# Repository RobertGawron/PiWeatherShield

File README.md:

# Pi Weather Shield

## Purpose

Low-cost, easy-to-build hat Raspberry Pi that turns it into an indoor weather station. On the hardware side, it's a simple PCB with sensors I2C parts (BME280 and Si7021) and a small OLED screen to show the meassurements: temperature, humidity, and air pressure. On the software side there is a Rust app that handles the data and can send them via MQTT for furthr processing (using tools like Graphana and Home asistant).

The project can be integrated with the [Home Environment Monitor](https://github.com/RobertGawron/HomeEnvironmentMonitor), adding real-time graphs of the meassurements accessible from phone or PC.

## Hardware

This project is straightforward and includes the following I2C components:

* **Si7021:**
    * Temperature
    * Relative humidity
* **SGP30:**
    * TVOC (Total Volatile Organic Compounds)
    * eCO2 (equivalent CO2)
    * Raw hydrogen (H2) signal
    * Raw ethanol signal
* **BME280:**
    * Temperature
    * Relative humidity
    * Atmospheric pressure
* **SSD1306:** 0.91-inch 128x32 OLED display.

Tools: KiCad.

[More info.](./Hardware/README.md)

## Installation

The application is quite simple (just a couple of Python scripts) and could easily be developed directly on the Raspberry Pi, which is probably what most people would do for a small project like this. However, I’ve chosen a different approach -one that might seem like overkill- but it allows me to learn and apply DevOps.

We'll set up a local Docker environment capable of cross-compiling Docker images that contain our application, which will then be deployed to the Raspberry Pi.

Using Ansible, we will preconfigure the Raspberry Pi (install Docker, enable I2C, etc.) and deploy the Docker images to the Pi automatically.

[More info.](./DevOps/README.md)

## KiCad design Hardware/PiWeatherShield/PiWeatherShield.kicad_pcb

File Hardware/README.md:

## Hardware Overview

#### I2C Addresses:

* Si7021: 0x40
* SGP30: 0x58
* BME280:
    * 0x76 (when the SDO pin is grounded)
    * 0x77 (when the SDO pin is connected to VCC)
* SSD1306: 0x3C or 0x3D, depending on the PCB design.

## Tools

The PCB diagram was designed using KiCad.

## Links

* [Raspberry Pi pinout](https://www.raspberrypi.com/documentation/computers/images/GPIO-Pinout-Diagram-2.png?hash=df7d7847c57a1ca6d5b2617695de6d46)

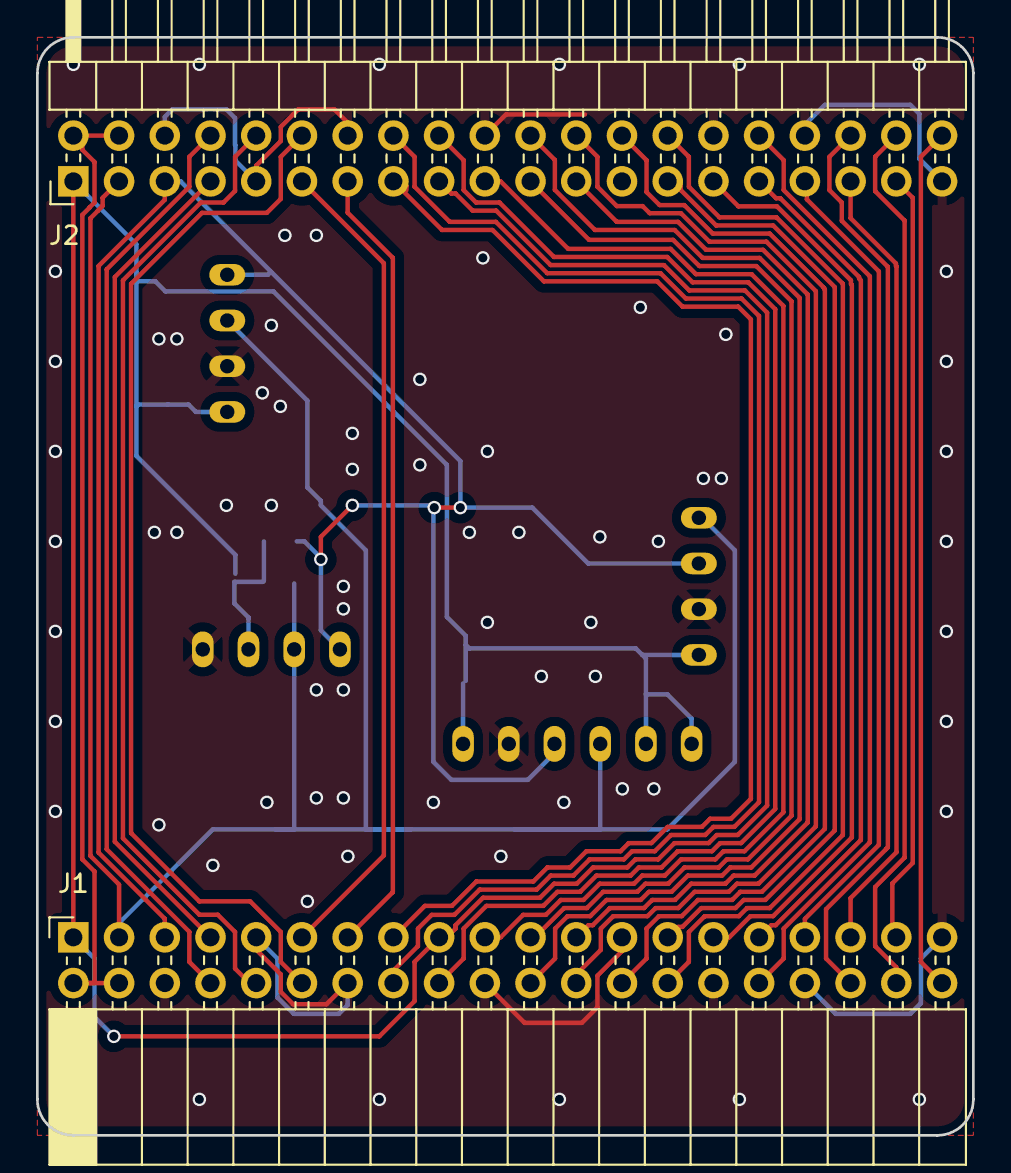
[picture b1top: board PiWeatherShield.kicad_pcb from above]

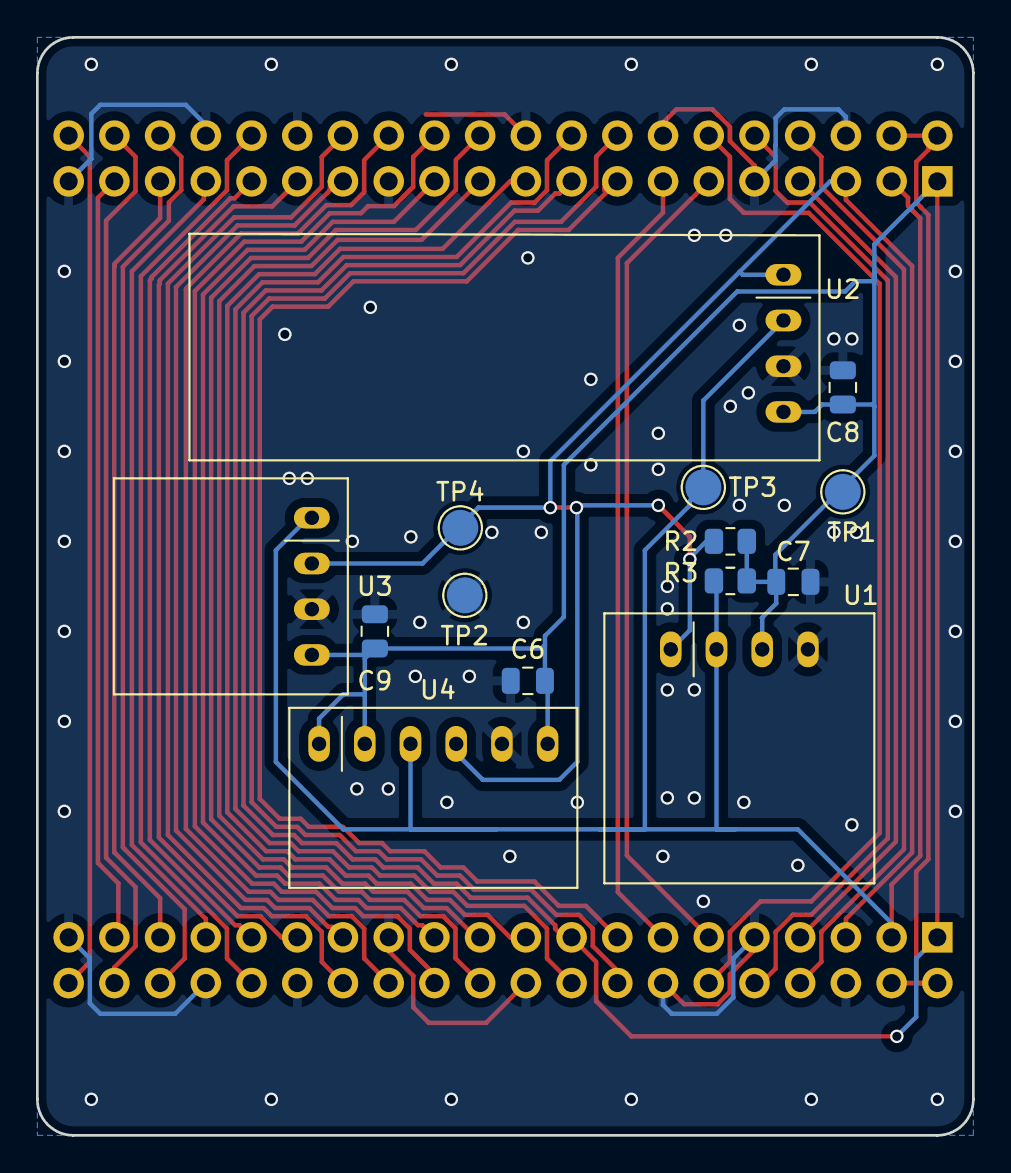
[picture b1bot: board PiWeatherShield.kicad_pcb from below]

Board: 2 copper layers, 52.0 x 61.0 mm, 16 parts (14 on the bottom side), 31 nets.

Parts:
C6, C7, C8, C9: 100n; C_0805_2012Metric
J1: Conn_02x20_Odd_Even; PinSocket_2x20_P2.54mm_Horizontal
J2: Conn_02x20_Odd_Even; PinHeader_2x20_P2.54mm_Horizontal
R2, R3: 2k2; R_0805_2012Metric
TP1, TP2, TP3, TP4: TestPoint; TestPoint_Pad_D2.0mm
U1: Si7021Board; SIP-4
U2: SSD1306DisplayBoard
U3: GY- SGP30/SGP40; GY- SGP30SGP40
U4: BME280Board

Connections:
+3.3V: C6.1, C7.1, C8.1, C9.1, J1.1, J1.17, J2.1, J2.17, R2.1, R3.1, TP1.1, U1.3 (VCC), U2.4 (VCC), U3.4 (VCC), U4.1 (SDD), U4.2 (CSB), U4.6 (VCC)
/5V: J1.2, J1.4, J2.2, J2.4
/GPIO0/ID_SD: J1.27, J2.27
/GPIO1: J1.28, J2.28
/GPIO2/SDA: J1.3, J2.3, R3.2, TP3.1, U1.2 (SDA), U2.2 (SDA), U3.1 (SDA), U4.3 (SDA)
/GPIO3/SCL: J1.5, J2.5, R2.2, TP4.1, U1.1 (SCL), U2.1 (SCL), U3.2 (SCL), U4.4 (SCL)
/GPIO4/GPCLK0: J1.7, J2.7
/GPIO5: J1.29, J2.29
/GPIO6: J1.31, J2.31
/GPIO7: J1.26, J2.26
/GPIO8: J1.24, J2.24
/GPIO9/MISO: J1.21, J2.21
/GPIO10/MOSI: J1.19, J2.19
/GPIO11/SCLK: J1.23, J2.23
/GPIO12: J1.32, J2.32
/GPIO13/PCM_FS: J1.35, J2.35
/GPIO13/PWM1: J1.33, J2.33
/GPIO14: J1.8, J2.8
/GPIO15: J1.10, J2.10
/GPIO16: J1.36, J2.36
/GPIO17: J1.11, J2.11
/GPIO18: J1.12, J2.12
/GPIO20: J1.38, J2.38
/GPIO21: J1.40, J2.40
/GPIO22: J1.15, J2.15
/GPIO23: J1.16, J2.16
/GPIO24: J1.18, J2.18
/GPIO25: J1.22, J2.22
/GPIO26: J1.37, J2.37
/GPIO27: J1.13, J2.13
GND: C6.2, C7.2, C8.2, C9.2, J1.6, J1.9, J1.14, J1.20, J1.25, J1.30, J1.34, J1.39, J2.6, J2.9, J2.14, J2.20, J2.25, J2.30, J2.34, J2.39, TP2.1, U1.4 (GND), U2.3 (GND), U3.3 (GND), U4.5 (GND)

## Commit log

2024-09-06 initial folder structure
2024-09-07 fix: #3
2024-09-21 build docker containers for rasbbery pi's in docker build container
2024-10-05 ansible draft
2025-08-23 init version
2025-08-30 mqtt
2025-08-30 xxxx
